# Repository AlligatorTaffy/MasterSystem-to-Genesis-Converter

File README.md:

# MasterSystem to Genesis Converter
 
Another CadSoft Eagle project using schematics found elsewhere.  Redesigned the boards to be fabricated.  This allows you to make the Sega Genesis backwards compatible with the previous Sega Master System with FM sound chip support.

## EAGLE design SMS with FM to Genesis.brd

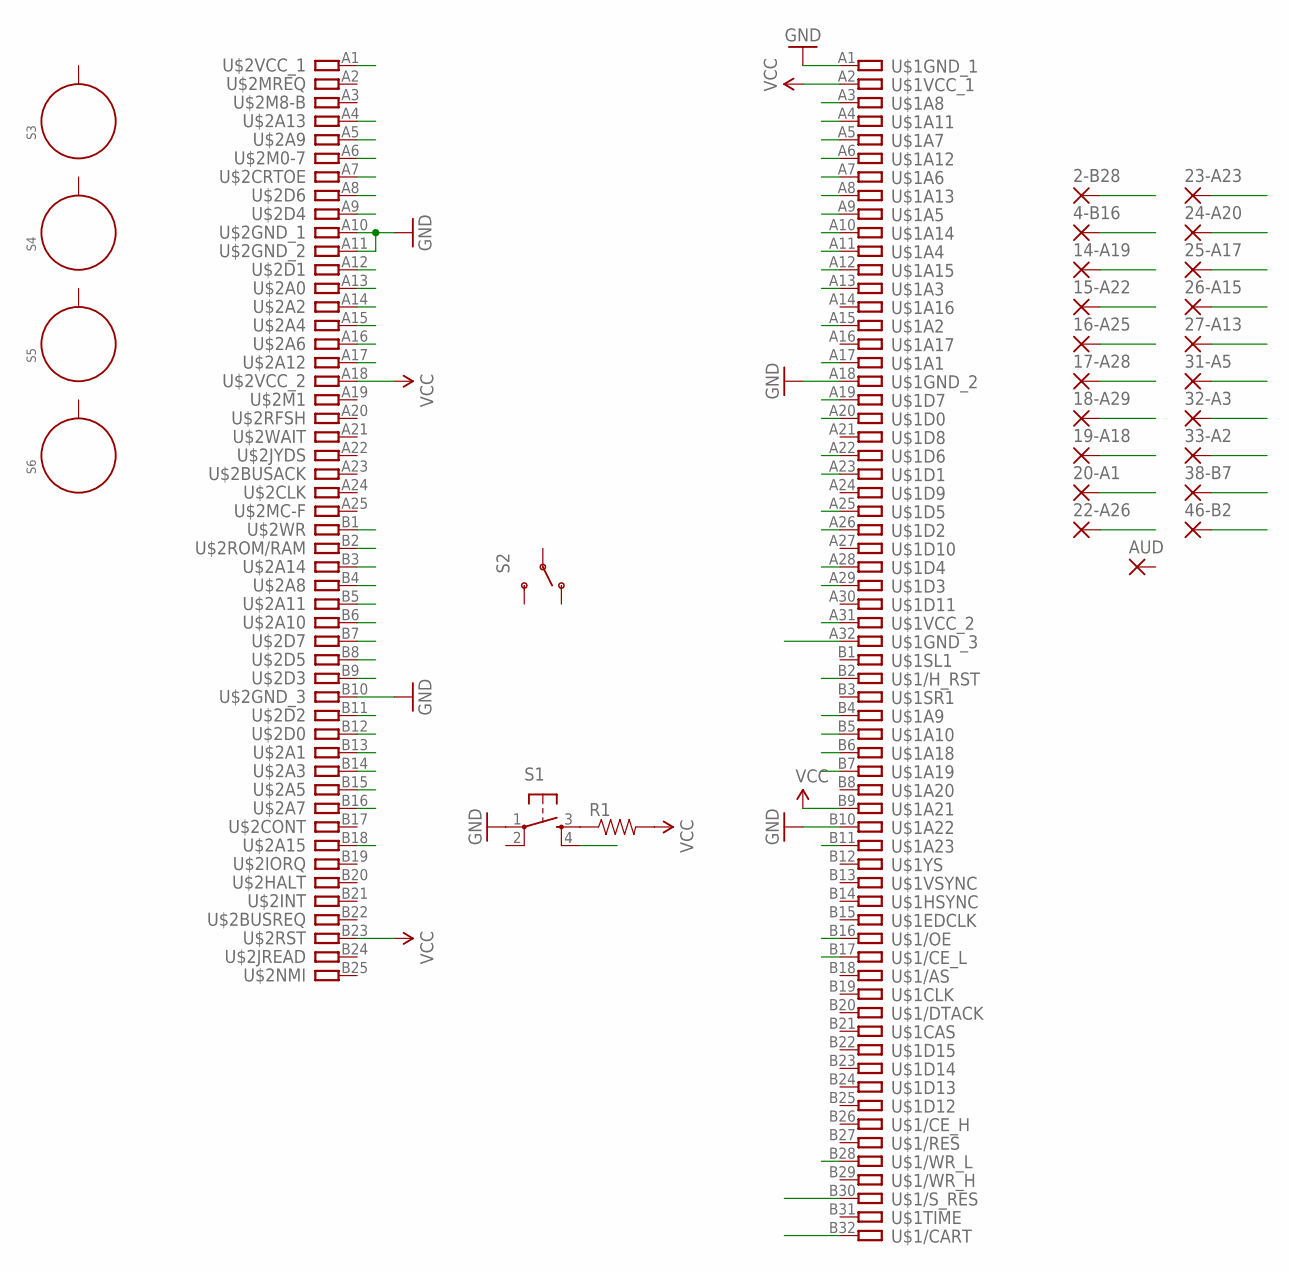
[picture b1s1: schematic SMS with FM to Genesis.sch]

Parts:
2-B28, 4-B16, 14-A19, 15-A22, 16-A25, 17-A28, 18-A29, 19-A18, 20-A1, 22-A26, 23-A23, 24-A20, 25-A17, 26-A15, 27-A13, 31-A5, 32-A3, 33-A2, 38-B7, 46-B2: WIREPADSMD1,27-254; SMD1,27-2,54
AUD: WIREPADSMD1,27-254; SMD1,27-2,54
R1: RESISTOR0805-RES; 0805
S1: TAC_SWITCHSMD; TACTILE-SWITCH-SMD
S2: SWITCH-SPDTPTH; SWITCH-SPDT
S3, S4, S5, S6: STANDOFF_ELECTRICAL; STANDOFF-ELECTRICAL
U$1: GENESIS-LARGE
U$2: SMS-R; SMS

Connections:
A3: 32-A3.1, U$1.A3, U$2.B16
A4: U$1.A4, U$2.B6
A5: 31-A5.1, U$1.A5, U$2.A16
A6: U$1.A6, U$2.B5
A7: U$1.A7, U$2.B15
A8: U$1.A8, U$2.A17
A9: U$1.A9, U$2.A15
A10: U$1.A10, U$2.A4
A11: U$1.A11, U$2.B14
A12: U$1.A12, U$2.B3
A13: 27-A13.1, U$1.A13, U$2.A14
A15: 26-A15.1, U$1.A15, U$2.B13
A17: 25-A17.1, U$1.A17, U$2.A13
A19: 14-A19.1, U$1.A19, U$2.B7
A20: 24-A20.1, U$1.A20, U$2.B12
A22: 15-A22.1, U$1.A22, U$2.A8
A23: 23-A23.1, U$1.A23, U$2.A12
A25: 16-A25.1, U$1.A25, U$2.B8
A26: 22-A26.1, U$1.A26, U$2.B11
A28: 17-A28.1, U$1.A28, U$2.A9
A29: 18-A29.1, U$1.A29, U$2.B9
A31: U$1.A31, U$2.A1
B2: 46-B2.1, U$1.B2
B4: U$1.B4, U$2.B4
B5: U$1.B5, U$2.A5
B6: U$1.B6, U$2.A7
B7: 38-B7.1, U$1.B7
B11: S1.4, U$1.B11
B16: 4-B16.1, U$1.B16, U$2.B2
B17: U$1.B17, U$2.A6, U$2.B18
B28: 2-B28.1, U$1.B28, U$2.B1
GND: 19-A18.1, 20-A1.1, S1.1, U$1.A1, U$1.A18, U$1.B10, U$2.A10, U$2.A11, U$2.B10
unnamed: R1.1, S1.3
SMS: U$1.A32, U$1.B30, U$1.B32
VCC: 33-A2.1, R1.2, U$1.A2, U$1.B9, U$2.A18, U$2.B23

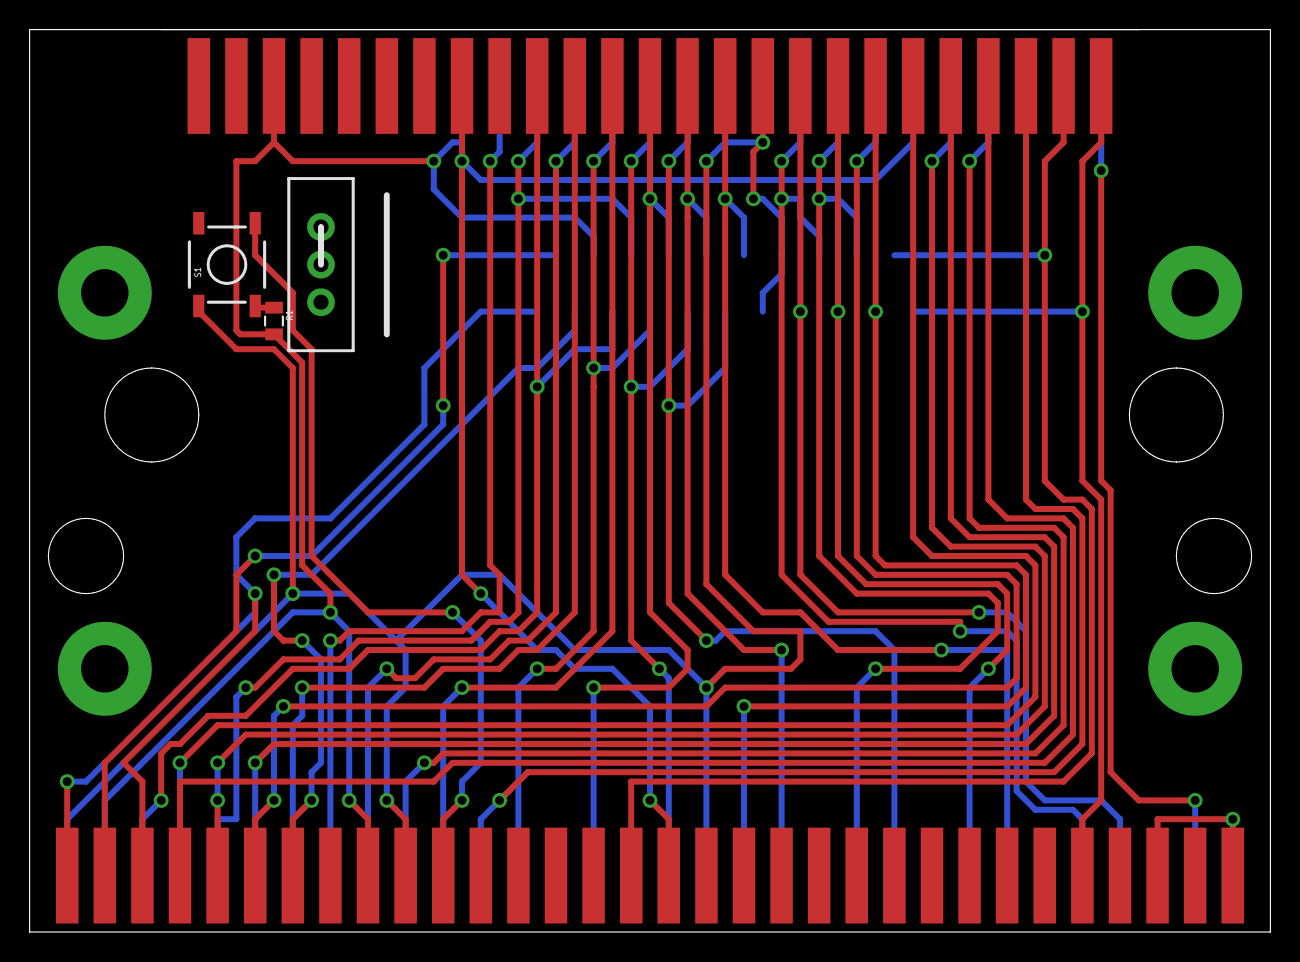
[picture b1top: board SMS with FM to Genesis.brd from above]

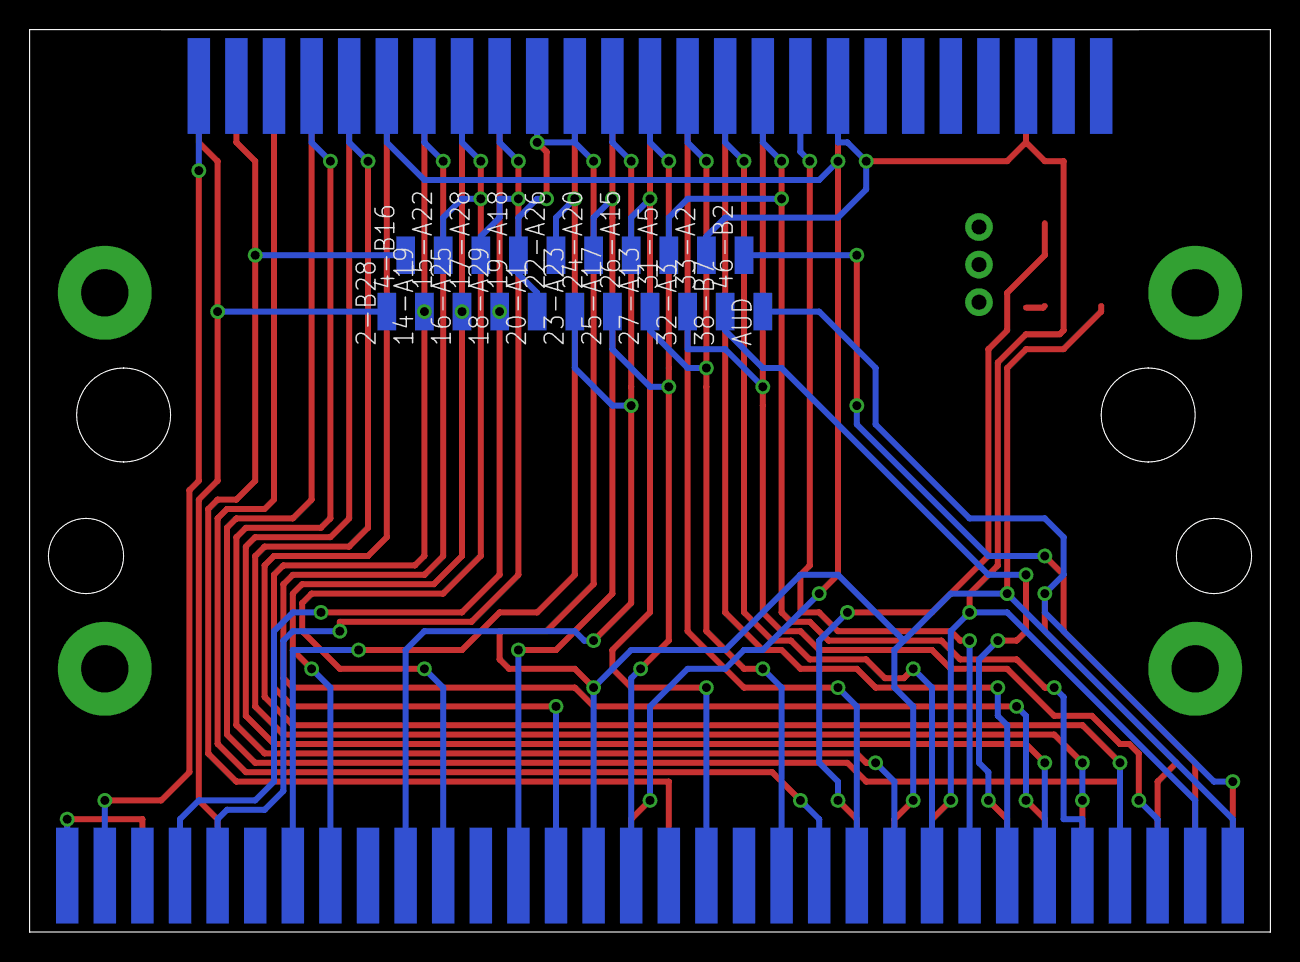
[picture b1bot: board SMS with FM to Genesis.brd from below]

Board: 2 copper layers, 83.8 x 61.0 mm, 30 parts (21 on the bottom side), 35 nets.

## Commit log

2023-05-29 Migrate to GitHub

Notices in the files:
parts and their libraries:
SparkFun-Electromechanical: Licensing: Creative Commons ShareAlike 4.0 International - https://creativecommons.org/licenses/by-sa/4.0
